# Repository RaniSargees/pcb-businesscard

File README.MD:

# PCB BUSINESS CARD

this project is a business card made of a circuit board with an 11x10 charlieplexed LED display.

The circuit board uses special construction techniques to achieve minimum thickness, such as mounting every component upside-down, through drilled holes.

this project is based on the HK32F030M microcontroller, which is obscure and poorly-documented (in english, at least), but very inexpensive

the total cost per card (purchased in medium-low volume) is ~$0.80CAD, which is high for a business card but still relatively cheap

# INCOMPLETE FIRMWARE

the firmware for this project is incomplete. the breakout game is unfinished, and I haven't even began working on pong, space invaders, and other games i wanted to add.

also, the font is a little unreadable on the display, which sort of defeats the purpose of this business card. I probably should have included my name and email in the silkscreen

---

still, uploading this for reference, perhaps someone can use this project as an example of how to set up keil for the hk32. that chip doesn't have much documentation, it seems everyone went for the risc-v based budget microcontrollers and not the ARM-based HK32 or PY32

# IMAGES

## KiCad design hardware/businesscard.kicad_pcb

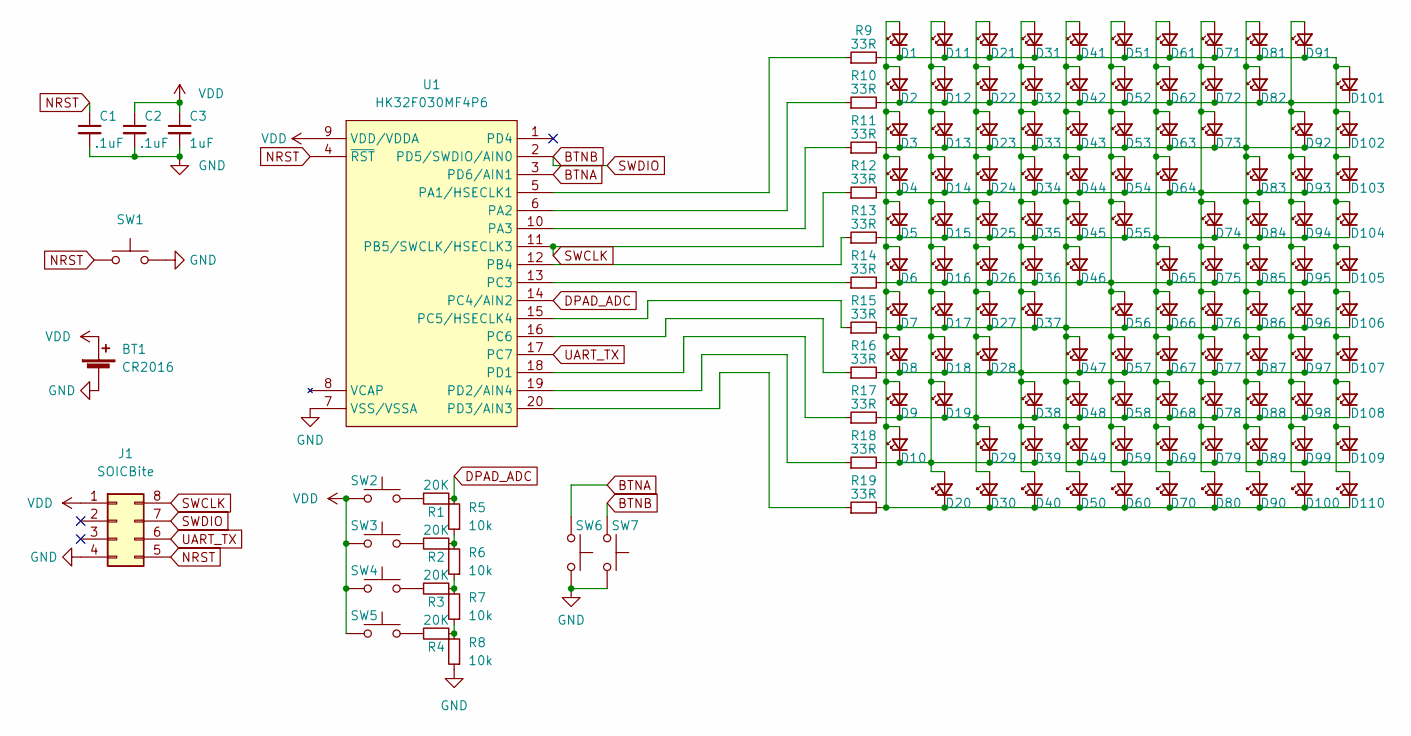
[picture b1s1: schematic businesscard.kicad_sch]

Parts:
BT1: CR2016; cr2016
C1, C2: .1uF; C_0402_1005Metric_Pad0.74x0.62mm_HandSolder
C3: 1uF; C_0402_1005Metric_Pad0.74x0.62mm_HandSolder
D1, D2, D3, D4, D5, D6, D7, D8, D9, D10, D11, D12, D13, D14, D15, D16, D17, D18, D19, D20, D21, D22, D23, D24, D25, D26, D27, D28, D29, D30, D31, D32, D33, D34, D35, D36, D37, D38, D39, D40, D41, D42, D43, D44, D45, D46, D47, D48, D49, D50, D51, D52, D53, D54, D55, D56, D57, D58, D59, D60, D61, D62, D63, D64, D65, D66, D67, D68, D69, D70, D71, D72, D73, D74, D75, D76, D77, D78, D79, D80, D81, D82, D83, D84, D85, D86, D87, D88, D89, D90, D91, D92, D93, D94, D95, D96, D97, D98, D99, D100, D101, D102, D103, D104, D105, D106, D107, D108, D109, D110: LED_Small; LED_0603_1608Metric_Pad1.05x0.95mm_HandSolder
J1: SOICBite; SOIC_clipProgSmall
R1, R2, R3, R4: 20K; R_0402_1005Metric_Pad0.72x0.64mm_HandSolder
R5, R6, R7, R8: 10k; R_0402_1005Metric_Pad0.72x0.64mm_HandSolder
R9, R10, R11, R12, R13, R14, R15, R16, R17, R18, R19: 33R; R_0402_1005Metric_Pad0.72x0.64mm_HandSolder
SW1: SW_Push; SW_3x4x2
SW2, SW3, SW4, SW5, SW6, SW7: SW_Push; SW_SPST_TSE024
U1: HK32F030MF4P6; TSSOP-20_4.4x6.5mm_P0.65mm

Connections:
BTNA: SW6.2, U1.3 (PD6/AIN1)
DPAD_ADC: R1.1, R5.2, U1.14 (PC4/AIN2)
GND: BT1.2 (-), C1.2, C2.2, C3.2, J1.4, R8.1, SW1.2, SW6.1, SW7.1, U1.7 (VSS/VSSA)
NRST: C1.1, J1.5, SW1.1, U1.4 (~RST)
unnamed: D1.1 (K), D11.1 (K), D21.1 (K), D31.1 (K), D41.1 (K), D51.1 (K), D61.1 (K), D71.1 (K), D81.1 (K), D91.1 (K), D101.2 (A), D102.2 (A), D103.2 (A), D104.2 (A), D105.2 (A), D106.2 (A), D107.2 (A), D108.2 (A), D109.2 (A), D110.2 (A), R9.2
unnamed: D1.2 (A), D2.2 (A), D3.2 (A), D4.2 (A), D5.2 (A), D6.2 (A), D7.2 (A), D8.2 (A), D9.2 (A), D10.2 (A), D20.1 (K), D30.1 (K), D40.1 (K), D50.1 (K), D60.1 (K), D70.1 (K), D80.1 (K), D90.1 (K), D100.1 (K), D110.1 (K), R19.2
unnamed: D10.1 (K), D11.2 (A), D12.2 (A), D13.2 (A), D14.2 (A), D15.2 (A), D16.2 (A), D17.2 (A), D18.2 (A), D19.2 (A), D20.2 (A), D29.1 (K), D39.1 (K), D49.1 (K), D59.1 (K), D69.1 (K), D79.1 (K), D89.1 (K), D99.1 (K), D109.1 (K), R18.2
unnamed: D2.1 (K), D12.1 (K), D22.1 (K), D32.1 (K), D42.1 (K), D52.1 (K), D62.1 (K), D72.1 (K), D82.1 (K), D91.2 (A), D92.2 (A), D93.2 (A), D94.2 (A), D95.2 (A), D96.2 (A), D97.2 (A), D98.2 (A), D99.2 (A), D100.2 (A), D101.1 (K), R10.2
unnamed: D3.1 (K), D13.1 (K), D23.1 (K), D33.1 (K), D43.1 (K), D53.1 (K), D63.1 (K), D73.1 (K), D81.2 (A), D82.2 (A), D83.2 (A), D84.2 (A), D85.2 (A), D86.2 (A), D87.2 (A), D88.2 (A), D89.2 (A), D90.2 (A), D92.1 (K), D102.1 (K), R11.2
unnamed: D4.1 (K), D14.1 (K), D24.1 (K), D34.1 (K), D44.1 (K), D54.1 (K), D64.1 (K), D71.2 (A), D72.2 (A), D73.2 (A), D74.2 (A), D75.2 (A), D76.2 (A), D77.2 (A), D78.2 (A), D79.2 (A), D80.2 (A), D83.1 (K), D93.1 (K), D103.1 (K), R12.2
unnamed: D5.1 (K), D15.1 (K), D25.1 (K), D35.1 (K), D45.1 (K), D55.1 (K), D61.2 (A), D62.2 (A), D63.2 (A), D64.2 (A), D65.2 (A), D66.2 (A), D67.2 (A), D68.2 (A), D69.2 (A), D70.2 (A), D74.1 (K), D84.1 (K), D94.1 (K), D104.1 (K), R13.2
unnamed: D6.1 (K), D16.1 (K), D26.1 (K), D36.1 (K), D46.1 (K), D51.2 (A), D52.2 (A), D53.2 (A), D54.2 (A), D55.2 (A), D56.2 (A), D57.2 (A), D58.2 (A), D59.2 (A), D60.2 (A), D65.1 (K), D75.1 (K), D85.1 (K), D95.1 (K), D105.1 (K), R14.2
unnamed: D7.1 (K), D17.1 (K), D27.1 (K), D37.1 (K), D41.2 (A), D42.2 (A), D43.2 (A), D44.2 (A), D45.2 (A), D46.2 (A), D47.2 (A), D48.2 (A), D49.2 (A), D50.2 (A), D56.1 (K), D66.1 (K), D76.1 (K), D86.1 (K), D96.1 (K), D106.1 (K), R15.2
unnamed: D8.1 (K), D18.1 (K), D28.1 (K), D31.2 (A), D32.2 (A), D33.2 (A), D34.2 (A), D35.2 (A), D36.2 (A), D37.2 (A), D38.2 (A), D39.2 (A), D40.2 (A), D47.1 (K), D57.1 (K), D67.1 (K), D77.1 (K), D87.1 (K), D97.1 (K), D107.1 (K), R16.2
unnamed: D9.1 (K), D19.1 (K), D21.2 (A), D22.2 (A), D23.2 (A), D24.2 (A), D25.2 (A), D26.2 (A), D27.2 (A), D28.2 (A), D29.2 (A), D30.2 (A), D38.1 (K), D48.1 (K), D58.1 (K), D68.1 (K), D78.1 (K), D88.1 (K), D98.1 (K), D108.1 (K), R17.2
unnamed: R1.2, SW2.1
unnamed: R2.2, SW3.1
unnamed: R3.2, SW4.1
unnamed: R4.2, SW5.1
unnamed: R2.1, R5.1, R6.2
unnamed: R3.1, R6.1, R7.2
unnamed: R4.1, R7.1, R8.2
unnamed: R9.1, U1.5 (PA1/HSECLK1)
unnamed: R10.1, U1.6 (PA2)
unnamed: R11.1, U1.10 (PA3)
unnamed: R13.1, U1.12 (PB4)
unnamed: R14.1, U1.13 (PC3)
unnamed: R15.1, U1.15 (PC5/HSECLK4)
unnamed: R16.1, U1.16 (PC6)
unnamed: R17.1, U1.18 (PC1)
unnamed: R18.1, U1.19 (PD2/AIN4)
unnamed: R19.1, U1.20 (PD3/AIN3)
SWCLK: J1.8, R12.1, U1.11 (PB5/SWCLK/HSECLK3)
SWDIO: J1.7, SW7.2, U1.2 (PD5/SWDIO/AIN0)
UART_TX: J1.6, U1.17 (PC7)
VDD: BT1.1 (+), C2.1, C3.1, J1.1, SW2.2, SW3.2, SW4.2, SW5.2, U1.9 (VDD/VDDA)

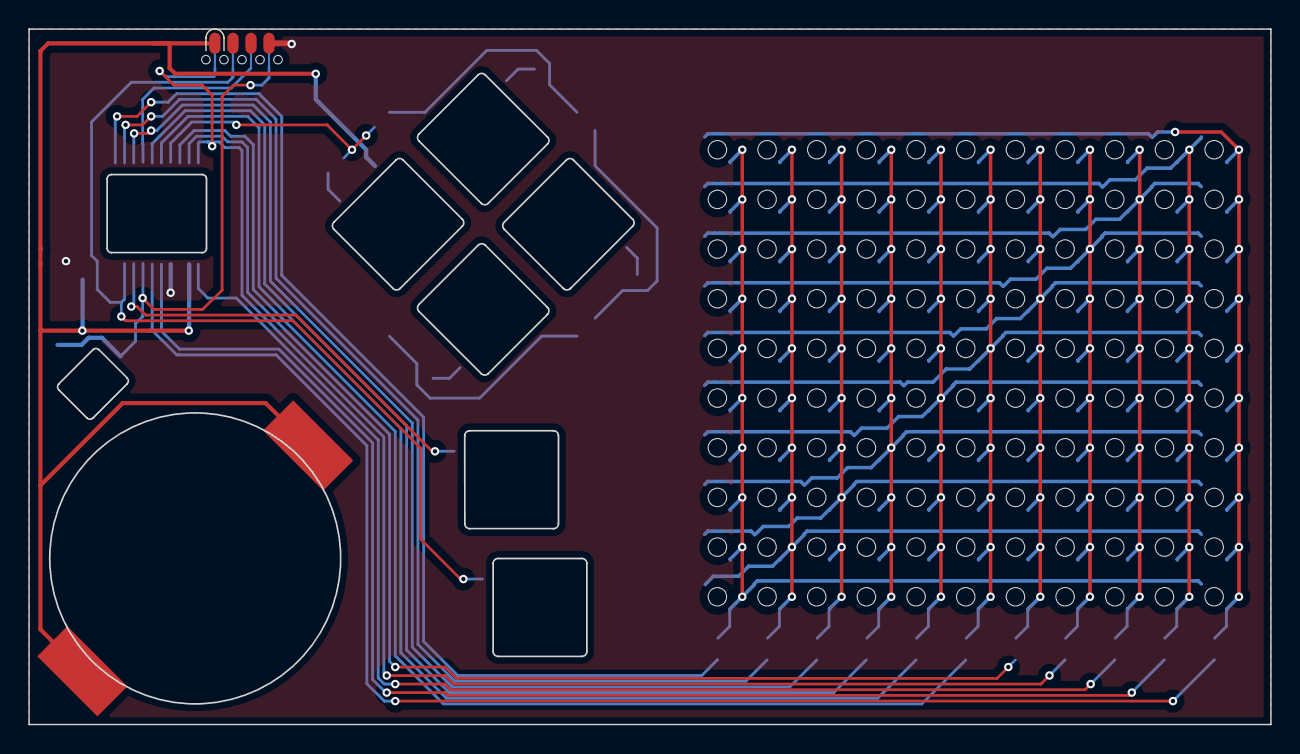
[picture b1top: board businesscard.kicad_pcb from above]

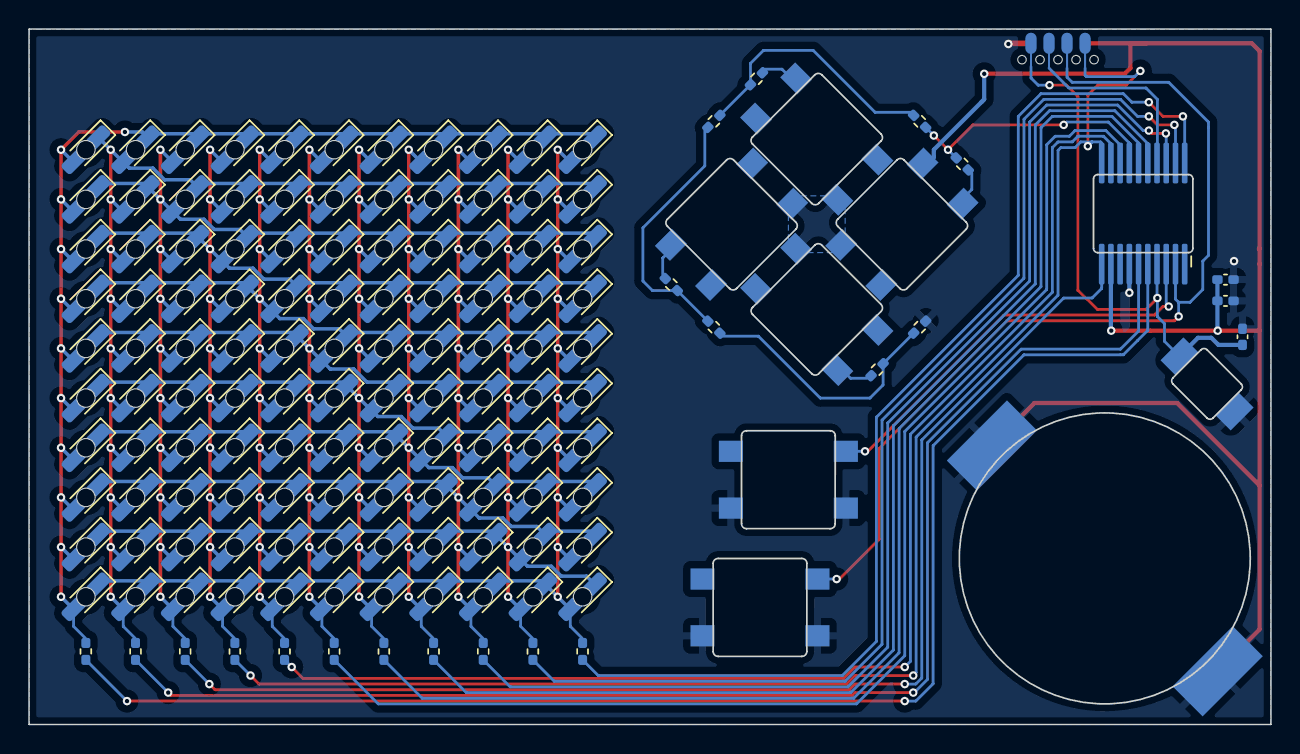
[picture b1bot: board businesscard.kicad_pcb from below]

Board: 2 copper layers, 87.5 x 49.0 mm, 142 parts (22 on the bottom side), 36 nets.

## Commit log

2025-02-18 dump files into repo
